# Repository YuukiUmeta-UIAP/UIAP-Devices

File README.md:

# Album of UIAP Devices

You can find everthing about UIAP Devices

- Source
- Library
- [Application](app)

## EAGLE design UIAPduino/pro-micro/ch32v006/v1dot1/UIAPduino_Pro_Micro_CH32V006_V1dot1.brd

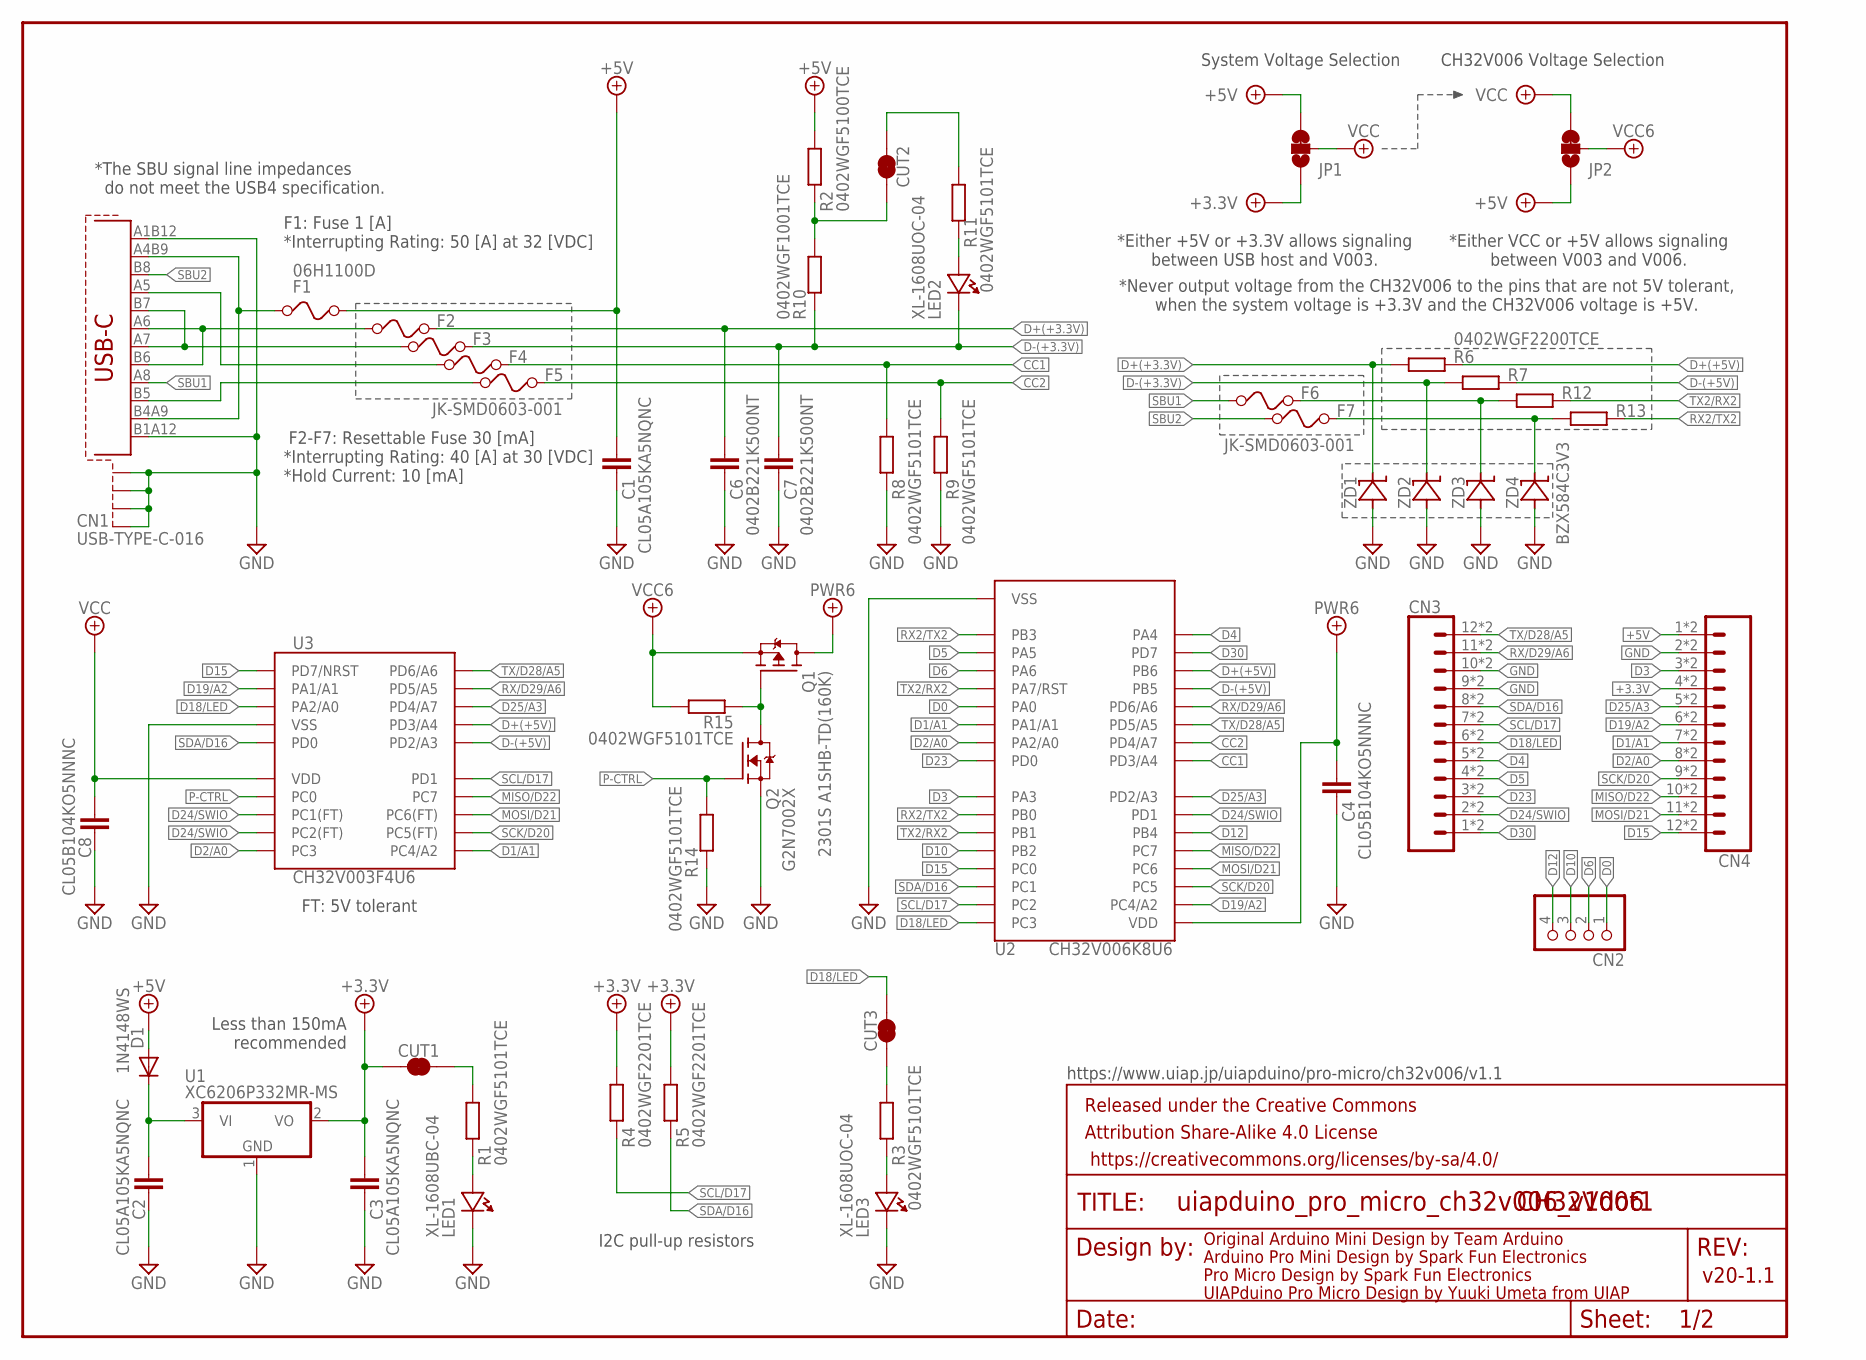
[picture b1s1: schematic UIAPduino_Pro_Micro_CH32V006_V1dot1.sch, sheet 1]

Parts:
C1, C2, C3: CL05A105KA5NQNC; 1005
C4, C8: CL05B104KO5NNNC; 1005
C6, C7: 0402B221K500NT; 1005
CN1: USB-TYPE-C-016
CN2: PH-2X2; 2X02
CN3, CN4: CONN_12CASTLE_0.9MM; 1X12_CASTELLATED_0.9MM
CUT1, CUT2, CUT3: SMT-JP-2-NC; SMT-JUMPER_2_NC_SILK_ROUND
D1: 1N4148WS; SOD-523
F1: 06H1100D; 1608
F2, F3, F4, F5, F6, F7: JK-SMD0603-001; 1608; JLCPCB-PART-# C2687114
FRAME1: FRAME-LETTER; CREATIVE_COMMONS
JP1, JP2: SMT-JP-3-NO-NC; SMT-JUMPER_3_1-NC_TRACE_SILK
LED1: XL-1608UBC-04; 1608-LED
LED2, LED3: XL-1608UOC-04; 1608-LED
Q1: 2301S A1SHB-TD(160K); SOT-23F_TOS-L
Q2: G2N7002X; SOT-523
R1, R3, R8, R9, R11, R14, R15: 0402WGF5101TCE; 1005
R2: 0402WGF5100TCE; 1005
R4, R5: 0402WGF2201TCE; 1005
R6, R7, R12, R13: 0402WGF2200TCE; 1005
R10: 0402WGF1001TCE; 1005
U1: XC6206P332MR-MS; SOT-23F_TOS-L
U2: CH32V006K8U6; QFN32-400X400X100
U3: CH32V003F4U6; QFN20-300X300X100-L
ZD1, ZD2, ZD3, ZD4: BZX584C3V3; SOD-523

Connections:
+3.3V: C3.1, CN4.4, CN4.4B (4), CUT1.2, JP1.1, R4.2, R5.2, U1.2 (VO)
+5V: C1.1, CN4.1, CN4.1B (1), D1.2 (A), F1.2, JP1.3, JP2.1, R2.2
CC1: F4.2, R8.2, U2.25 (PD3/A4)
CC2: F5.2, R9.2, U2.26 (PD4/A7)
CUT1: CUT1.1, R1.2
D0: CN2.1, U2.5 (PA0)
D1: C2.1, D1.1 (C), U1.3 (VI)
D1/A1: CN4.7, CN4.7B (7), U2.6 (PA1/A1), U3.11 (PC4/A2)
D2/A0: CN4.8, CN4.8B (8), U2.7 (PA2/A0), U3.10 (PC3)
D3: CN4.3, CN4.3B (3), U2.9 (PA3)
D4: CN3.5, CN3.5B (5), U2.32 (PA4)
D5: CN3.4, CN3.4B (4), U2.2 (PA5)
D6: CN2.2, U2.3 (PA6)
D10: CN2.3, U2.12 (PB2)
D12: CN2.4, U2.22 (PB4)
D15: CN4.12, CN4.12B (12), U2.13 (PC0), U3.1 (PD7/NRST)
D18/LED: CN3.6, CN3.6B (6), CUT3.1, U2.16 (PC3), U3.3 (PA2/A0)
D19/A2: CN4.6, CN4.6B (6), U2.18 (PC4/A2), U3.2 (PA1/A1)
D23: CN3.3, CN3.3B (3), U2.8 (PD0)
D24/SWIO: CN3.2, CN3.2B (2), U2.23 (PD1), U3.8 (PC1(FT)), U3.9 (PC2(FT))
D25/A3: CN4.5, CN4.5B (5), U2.24 (PD2/A3), U3.18 (PD4/A7)
D30: CN3.1, CN3.1B (1), U2.31 (PD7)
D+(+3.3V): C6.1, F2.2, R6.1, ZD1.1 (C)
D+(+5V): R6.2, U2.30 (PB6), U3.17 (PD3/A4)
D-(+3.3V): C7.1, F3.2, LED2.2 (C), R7.1, R10.1, ZD2.1 (C)
D-(+5V): R7.2, U2.29 (PB5), U3.16 (PD2/A3)
F1: CN1.A4B9 (VBUS), CN1.B4A9 (VBUS), F1.1
GND: C1.2, C2.2, C3.2, C4.2, C6.2, C7.2, C8.2, CN1.A1B12 (GND), CN1.B1A12 (GND), CN1.S1, CN1.S1B (S1), CN1.S2, CN1.S2B (S2), CN1.S3, CN1.S3B (S3), CN1.S4, CN1.S4B (S4), CN3.9, CN3.9B (9), CN3.10, CN3.10B (10), CN4.2, CN4.2B (2), LED1.2 (C), LED3.2 (C), Q2.2 (S), R8.1, R9.1, R14.1, U1.1 (GND), U2.0 (VSS), U2.P-VIA$1 (VSS), U2.P-VIA$5 (VSS), U2.P-VIA$6 (VSS), U2.P-VIA$8 (VSS), U2.P-VIA$9 (VSS), U3.4 (VSS), U3.21 (VSS), U3.P-VIA$1 (VSS), ZD1.2 (A), ZD2.2 (A), ZD3.2 (A), ZD4.2 (A)
MISO/D22: CN4.10, CN4.10B (10), U2.21 (PC7), U3.14 (PC7)
MOSI/D21: CN4.11, CN4.11B (11), U2.20 (PC6), U3.13 (PC6(FT))
unnamed: CN1.A6 (DP1), CN1.B6 (DP2), F2.1
unnamed: CUT2.2, R2.1, R10.2
unnamed: Q1.1 (G), Q2.3 (D), R15.1
unnamed: CN1.A7 (DN1), CN1.B7 (DN2), F3.1
unnamed: CN1.A5 (CC1), F4.1
unnamed: F6.2, R12.1, ZD3.1 (C)
unnamed: LED3.1 (A), R3.1
unnamed: CN1.B5 (CC2), F5.1
unnamed: LED2.1 (A), R11.1
unnamed: CUT3.2, R3.2
unnamed: CUT2.1, R11.2
unnamed: F7.2, R13.1, ZD4.1 (C)
unnamed: LED1.1 (A), R1.1
P-CTRL: Q2.1 (G), R14.2, U3.7 (PC0)
PWR6: C4.1, Q1.3 (D), U2.17 (VDD)
RX2/TX2: R13.2, U2.1 (PB3), U2.10 (PB0)
RX/D29/A6: CN3.11, CN3.11B (11), U2.28 (PD6/A6), U3.19 (PD5/A5)
SBU1: CN1.A8 (SBU1), F6.1
SBU2: CN1.B8 (SBU2), F7.1
SCK/D20: CN4.9, CN4.9B (9), U2.19 (PC5), U3.12 (PC5(FT))
SCL/D17: CN3.7, CN3.7B (7), R4.1, U2.15 (PC2), U3.15 (PD1)
SDA/D16: CN3.8, CN3.8B (8), R5.1, U2.14 (PC1), U3.5 (PD0)
TX2/RX2: R12.2, U2.4 (PA7/RST), U2.11 (PB1)
TX/D28/A5: CN3.12, CN3.12B (12), U2.27 (PD5/A5), U3.20 (PD6/A6)
VCC: C8.1, JP1.2, JP2.3, U3.6 (VDD)
VCC6: JP2.2, Q1.2 (S), R15.2

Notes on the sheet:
Original Arduino Mini Design by Team Arduino
Arduino Pro Mini Design by Spark Fun Electronics
Less than 150mA recommended
Pro Micro Design by Spark Fun Electronics
CH32V006 Voltage Selection
v20-1.1
F2-F7: Resettable Fuse 30 [mA] *Interrupting Rating: 40 [A] at 30 [VDC] *Hold Current: 10 [mA]
I2C pull-up resistors
UIAPduino Pro Micro Design by Yuuki Umeta from UIAP
https://www.uiap.jp/uiapduino/pro-micro/ch32v006/v1.1
F1: Fuse 1 [A] *Interrupting Rating: 50 [A] at 32 [VDC]
*Either +5V or +3.3V allows signaling between USB host and V003.
CH32V006
System Voltage Selection
*Either VCC or +5V allows signaling between V003 and V006.
FT: 5V tolerant
*Never output voltage from the CH32V006 to the pins that are not 5V tolerant, when the system voltage is +3.3V and the CH32V006 voltage is +5V.
*The SBU signal line impedances do not meet the USB4 specification.

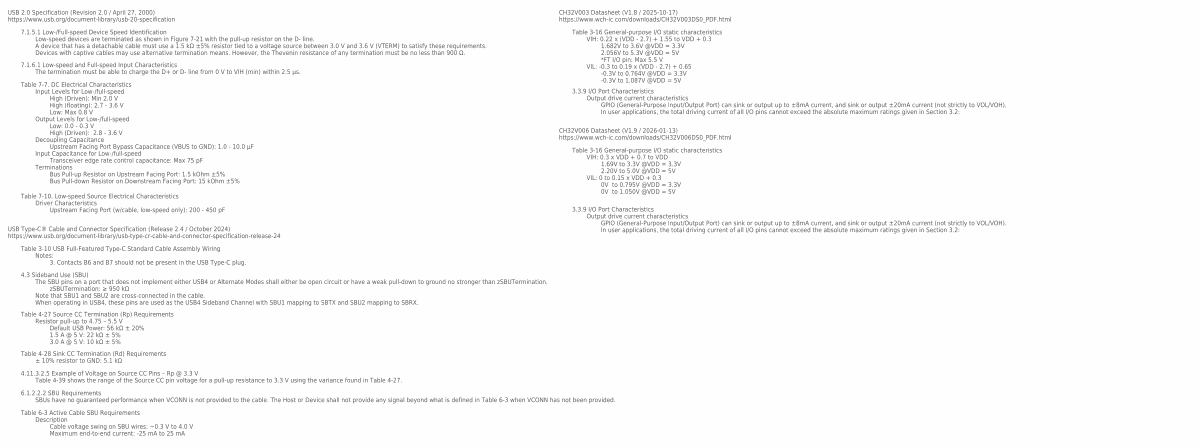
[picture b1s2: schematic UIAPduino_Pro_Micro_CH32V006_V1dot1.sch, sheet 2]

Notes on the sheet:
Table 7-10. Low-speed Source Electrical Characteristics Driver Characteristics Upstream Facing Port (w/cable, low-speed only): 200 - 450 pF
Table 7-7. DC Electrical Characteristics Input Levels for Low-/full-speed High (Driven): Min 2.0 V High (floating): 2.7 - 3.6 V Low: Max 0.8 V Output Levels for Low-/full-speed Low: 0.0 - 0.3 V High (Driven): 2.8 - 3.6 V Decoupling Capacitance Upstream Facing Port Bypass Capacitance (VBUS to GND): 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
7.1.6.1 Low-speed and Full-speed Input Characteristics The termination must be able to charge the D+ or D- line from 0 V to VIH (min) within 2.5 µs.
7.1.5.1 Low-/Full-speed Device Speed Identification Low-speed devices are terminated as shown in Figure 7-21 with the pull-up resistor on the D- line. A device that has a detachable cable must use a 1.5 kΩ ±5% resistor tied to a voltage source between 3.0 V and 3.6 V (VTERM) to satisfy these requir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
Table 4-28 Sink CC Termination (Rd) Requirements ± 10% resistor to GND: 5.1 kΩ
Table 4-27 Source CC Termination (Rp) Requirements Resistor pull-up to 4.75 – 5.5 V Default USB Power: 56 kΩ ± 20% 1.5 A @ 5 V: 22 kΩ ± 5% 3.0 A @ 5 V: 10 kΩ ± 5%
USB Type-C® Cable and Connector Specification (Release 2.4 / October 2024) https://www.usb.org/document-library/usb-type-cr-cable-and-connector-specification-release-24
USB 2.0 Specification (Revision 2.0 / April 27, 2000) https://www.usb.org/document-library/usb-20-specification
4.11.3.2.5 Example of Voltage on Source CC Pins – Rp @ 3.3 V Table 4-39 shows the range of the Source CC pin voltage for a pull-up resistance to 3.3 V using the variance found in Table 4-27.
CH32V006 Datasheet (V1.9 / 2026-01-13) https://www.wch-ic.com/downloads/CH32V006DS0_PDF.html
Table 3-16 General-purpose I/O static characteristics VIH: 0.3 x VDD + 0.7 to VDD 1.69V to 3.3V @VDD = 3.3V 2.20V to 5.0V @VDD = 5V VIL: 0 to 0.15 x VDD + 0.3 0V to 0.795V @VDD = 3.3V 0V to 1.050V @VDD = 5V
Table 3-10 USB Full-Featured Type-C Standard Cable Assembly Wiring Notes: 3. Contacts B6 and B7 should not be present in the USB Type-C plug.
4.3 Sideband Use (SBU) The SBU pins on a port that does not implement either USB4 or Alternate Modes shall either be open circuit or have a weak pull-down to ground no stronger than zSBUTermination. zSBUTermination: ≥ 950 kΩ Note that SBU1 and SBU2 are cross-connected in the cable. When operating i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
3.3.9 I/O Port Characteristics Output drive current characteristics GPIO (General-Purpose Input/Output Port) can sink or output up to ±8mA current, and sink or output ±20mA current (not strictly to VOL/VOH). In user applications, the total driving current of all I/O pins cannot exceed the absolute 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
6.1.2.2.2 SBU Requirements SBUs have no guaranteed performance when VCONN is not provided to the cable. The Host or Device shall not provide any signal beyond what is defined in Table 6-3 when VCONN has not been provided.
Table 6-3 Active Cable SBU Requirements Description Cable voltage swing on SBU wires: −0.3 V to 4.0 V Maximum end-to-end current: -25 mA to 25 mA
CH32V003 Datasheet (V1.8 / 2025-10-17) https://www.wch-ic.com/downloads/CH32V003DS0_PDF.html
Table 3-16 General-purpose I/O static characteristics VIH: 0.22 x (VDD - 2.7) + 1.55 to VDD + 0.3 1.682V to 3.6V @VDD = 3.3V 2.056V to 5.3V @VDD = 5V *FT I/O pin: Max 5.5 V VIL: -0.3 to 0.19 x (VDD - 2.7) + 0.65 -0.3V to 0.764V @VDD = 3.3V -0.3V to 1.087V @VDD = 5V

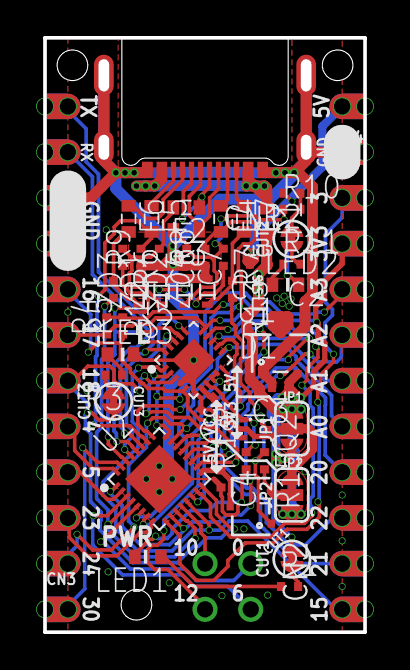
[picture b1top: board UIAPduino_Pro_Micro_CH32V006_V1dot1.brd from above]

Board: 2 copper layers, 17.8 x 33.0 mm, 52 parts (0 on the bottom side), 56 nets.

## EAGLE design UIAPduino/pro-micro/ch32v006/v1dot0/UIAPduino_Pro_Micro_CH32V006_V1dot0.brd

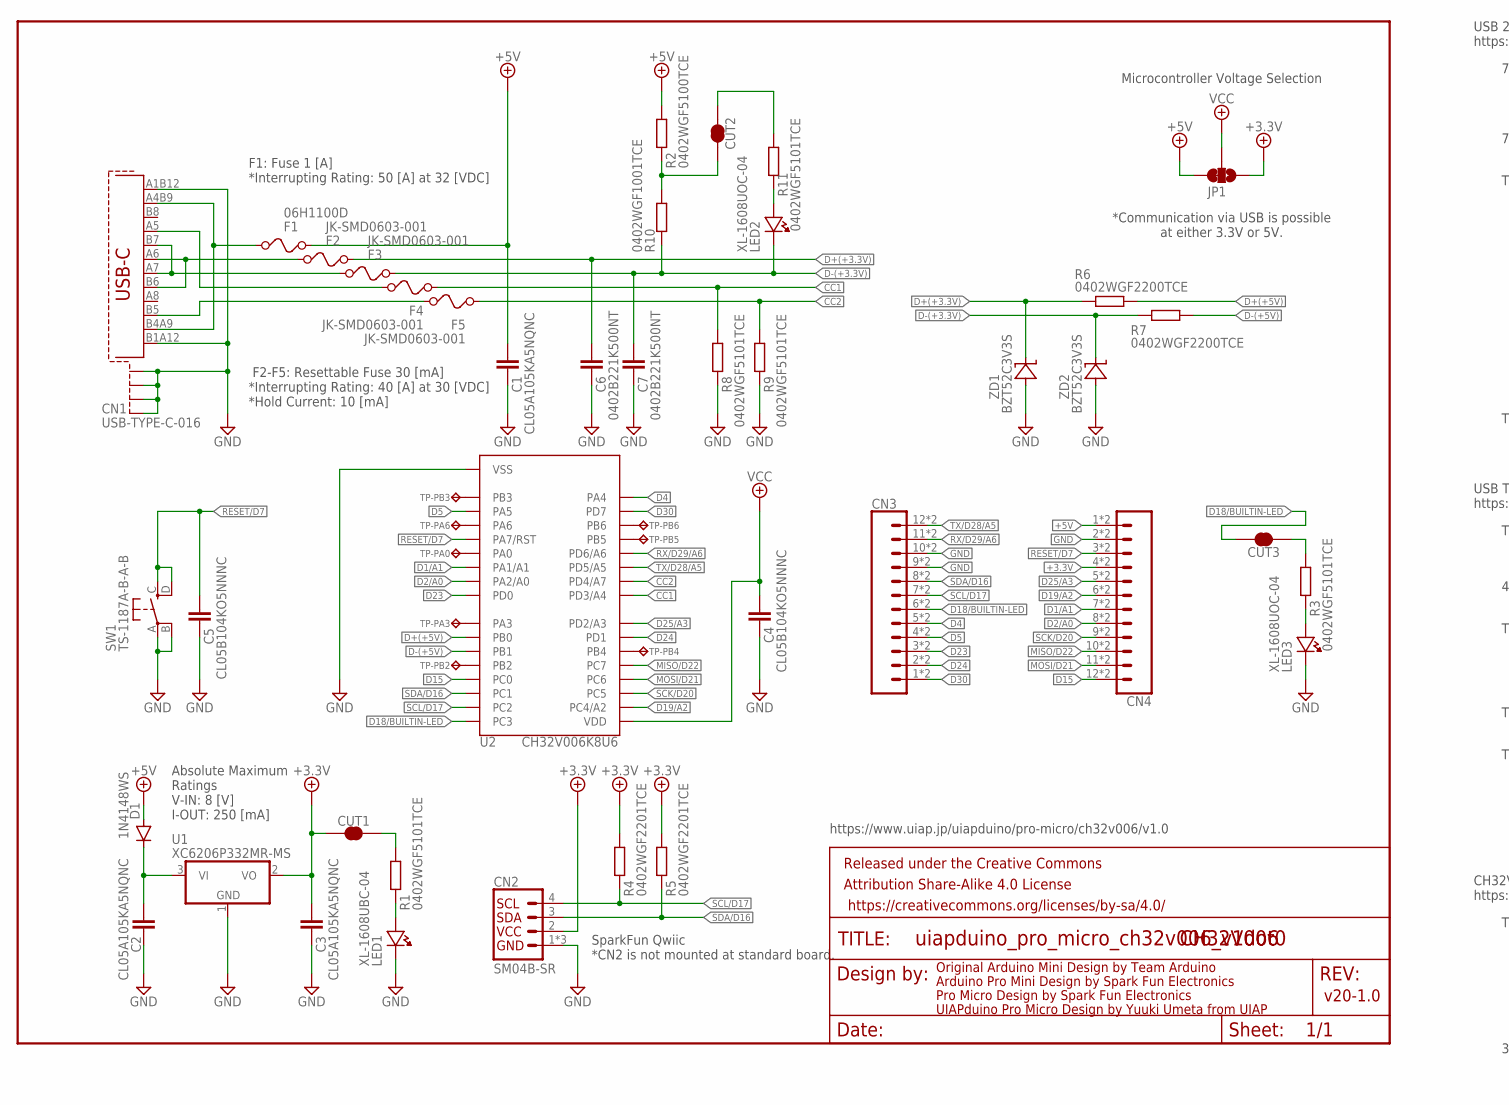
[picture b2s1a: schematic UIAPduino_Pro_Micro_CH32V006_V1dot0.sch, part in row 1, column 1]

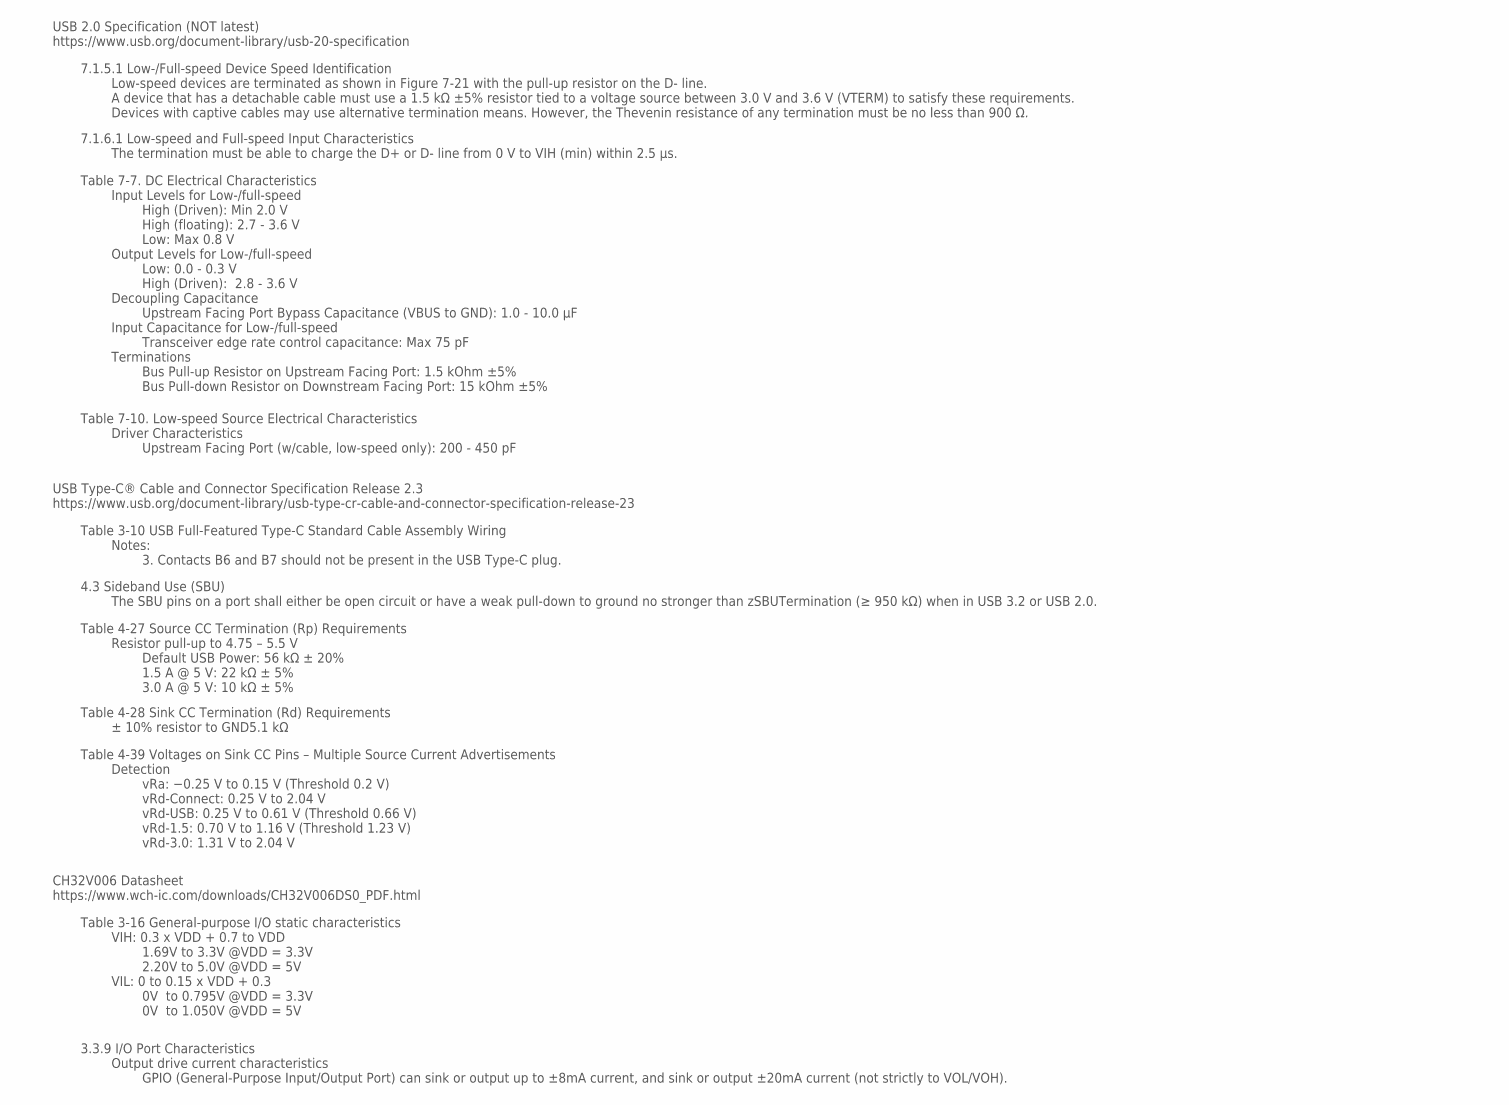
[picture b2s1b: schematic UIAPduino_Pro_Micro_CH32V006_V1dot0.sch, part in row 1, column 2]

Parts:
C1, C2, C3: CL05A105KA5NQNC; 1005
C4, C5: CL05B104KO5NNNC; 1005
C6, C7: 0402B221K500NT; 1005
CN1: USB-TYPE-C-016
CN2: SM04B-SR; JST04_1MM_RA
CN3, CN4: CONN_12CASTLE_0.9MM; 1X12_CASTELLATED_0.9MM
CUT1, CUT2, CUT3: SMT-JP-2-NC; SMT-JUMPER_2_NC_SILK_ROUND
D1: 1N4148WS; SOD323-R; JLCPCB-PART-# C2128
F1: 06H1100D; 1608
F2, F3, F4, F5: JK-SMD0603-001; 1608
FRAME1: FRAME-LETTER; CREATIVE_COMMONS
JP1: SMT-JP-3-NO-NC; SMT-JUMPER_3_1-NC_TRACE_SILK
LED1: XL-1608UBC-04; 1608-LED
LED2, LED3: XL-1608UOC-04; 1608-LED
R1, R3, R8, R9, R11: 0402WGF5101TCE; 1005
R2: 0402WGF5100TCE; 1005
R4, R5: 0402WGF2201TCE; 1005
R6, R7: 0402WGF2200TCE; 1005
R10: 0402WGF1001TCE; 1005
SW1: TS-1187A-B-A-B
TP-PA0, TP-PA3, TP-PA6: TPTP06R; TP06R
TP-PB2, TP-PB3, TP-PB4, TP-PB5, TP-PB6: TPTP06R; TP06R
U1: XC6206P332MR-MS; SOT-23F_TOS
U2: CH32V006K8U6; QFN40P400X400X100-33T270
ZD1, ZD2: BZT52C3V3S; SOD323-R

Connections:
+3.3V: C3.1, CN2.2, CN4.4, CN4.4B (4), CUT1.2, JP1.1, R4.2, R5.2, U1.2 (VO)
+5V: C1.1, CN4.1, CN4.1B (1), D1.A, F1.2, JP1.3, R2.2
CC1: F4.2, R8.2, U2.25 (PD3/A4)
CC2: F5.2, R9.2, U2.26 (PD4/A7)
D1/A1: CN4.7, CN4.7B (7), U2.6 (PA1/A1)
D2/A0: CN4.8, CN4.8B (8), U2.7 (PA2/A0)
D4: CN3.5, CN3.5B (5), U2.32 (PA4)
D5: CN3.4, CN3.4B (4), U2.2 (PA5)
D15: CN4.12, CN4.12B (12), U2.13 (PC0)
D18/BUILTIN-LED: CN3.6, CN3.6B (6), CUT3.1, U2.16 (PC3)
D19/A2: CN4.6, CN4.6B (6), U2.18 (PC4/A2)
D23: CN3.3, CN3.3B (3), U2.8 (PD0)
D24: CN3.2, CN3.2B (2), U2.23 (PD1)
D25/A3: CN4.5, CN4.5B (5), U2.24 (PD2/A3)
D30: CN3.1, CN3.1B (1), U2.31 (PD7)
D+(+3.3V): C6.1, F2.2, R6.1, ZD1.C
D+(+5V): R6.2, U2.10 (PB0)
D-(+3.3V): C7.1, F3.2, LED2.2 (C), R7.1, R10.1, ZD2.C
D-(+5V): R7.2, U2.11 (PB1)
F1: CN1.A4B9 (VBUS), CN1.B4A9 (VBUS), F1.1
GND: C1.2, C2.2, C3.2, C4.2, C5.2, C6.2, C7.2, CN1.A1B12 (GND), CN1.B1A12 (GND), CN1.S1, CN1.S1B (S1), CN1.S2, CN1.S2B (S2), CN1.S3, CN1.S3B (S3), CN1.S4, CN1.S4B (S4), CN2.1, CN2.NC1 (1), CN2.NC2 (1), CN3.9, CN3.9B (9), CN3.10, CN3.10B (10), CN4.2, CN4.2B (2), LED1.2 (C), LED3.2 (C), R8.1, R9.1, SW1.A, SW1.B (P1), U1.1 (GND), U2.0 (VSS), U2.P-VIA$1 (VSS), U2.P-VIA$2 (VSS), U2.P-VIA$3 (VSS), U2.P-VIA$4 (VSS), U2.P-VIA$5 (VSS), U2.P-VIA$6 (VSS), U2.P-VIA$7 (VSS), U2.P-VIA$8 (VSS), U2.P-VIA$9 (VSS), ZD1.A, ZD2.A
MISO/D22: CN4.10, CN4.10B (10), U2.21 (PC7)
MOSI/D21: CN4.11, CN4.11B (11), U2.20 (PC6)
unnamed: CN1.A6 (DP1), CN1.B6 (DP2), F2.1
unnamed: CUT2.2, R2.1, R10.2
unnamed: C2.1, D1.C, U1.3 (VI)
unnamed: CN1.A7 (DN1), CN1.B7 (DN2), F3.1
unnamed: CN1.A5 (CC1), F4.1
unnamed: CUT1.1, R1.2
unnamed: LED3.1 (A), R3.1
unnamed: CN1.B5 (CC2), F5.1
unnamed: LED2.1 (A), R11.1
unnamed: CUT3.2, R3.2
unnamed: CUT2.1, R11.2
unnamed: TP-PB3.TP, U2.1 (PB3)
unnamed: TP-PA6.TP, U2.3 (PA6)
unnamed: TP-PA0.TP, U2.5 (PA0)
unnamed: TP-PA3.TP, U2.9 (PA3)
unnamed: TP-PB2.TP, U2.12 (PB2)
unnamed: TP-PB4.TP, U2.22 (PB4)
unnamed: TP-PB5.TP, U2.29 (PB5)
unnamed: TP-PB6.TP, U2.30 (PB6)
unnamed: LED1.1 (A), R1.1
RESET/D7: C5.1, CN4.3, CN4.3B (3), SW1.C (S), SW1.D (S1), U2.4 (PA7/RST)
RX/D29/A6: CN3.11, CN3.11B (11), U2.28 (PD6/A6)
SCK/D20: CN4.9, CN4.9B (9), U2.19 (PC5)
SCL/D17: CN2.4, CN3.7, CN3.7B (7), R4.1, U2.15 (PC2)
SDA/D16: CN2.3, CN3.8, CN3.8B (8), R5.1, U2.14 (PC1)
TX/D28/A5: CN3.12, CN3.12B (12), U2.27 (PD5/A5)
VCC: C4.1, JP1.2, U2.17 (VDD)

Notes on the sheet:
Original Arduino Mini Design by Team Arduino
Arduino Pro Mini Design by Spark Fun Electronics
Absolute Maximum Ratings V-IN: 8 [V] I-OUT: 250 [mA]
Pro Micro Design by Spark Fun Electronics
Microcontroller Voltage Selection
v20-1.0
F2-F5: Resettable Fuse 30 [mA] *Interrupting Rating: 40 [A] at 30 [VDC] *Hold Current: 10 [mA]
Table 7-10. Low-speed Source Electrical Characteristics Driver Characteristics Upstream Facing Port (w/cable, low-speed only): 200 - 450 pF
Table 7-7. DC Electrical Characteristics Input Levels for Low-/full-speed High (Driven): Min 2.0 V High (floating): 2.7 - 3.6 V Low: Max 0.8 V Output Levels for Low-/full-speed Low: 0.0 - 0.3 V High (Driven): 2.8 - 3.6 V Decoupling Capacitance Upstream Facing Port Bypass Capacitance (VBUS to GND): 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
7.1.6.1 Low-speed and Full-speed Input Characteristics The termination must be able to charge the D+ or D- line from 0 V to VIH (min) within 2.5 µs.
7.1.5.1 Low-/Full-speed Device Speed Identification Low-speed devices are terminated as shown in Figure 7-21 with the pull-up resistor on the D- line. A device that has a detachable cable must use a 1.5 kΩ ±5% resistor tied to a voltage source between 3.0 V and 3.6 V (VTERM) to satisfy these requir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
Table 4-28 Sink CC Termination (Rd) Requirements ± 10% resistor to GND5.1 kΩ
Table 4-27 Source CC Termination (Rp) Requirements Resistor pull-up to 4.75 – 5.5 V Default USB Power: 56 kΩ ± 20% 1.5 A @ 5 V: 22 kΩ ± 5% 3.0 A @ 5 V: 10 kΩ ± 5%
USB Type-C® Cable and Connector Specification Release 2.3 https://www.usb.org/document-library/usb-type-cr-cable-and-connector-specification-release-23
USB 2.0 Specification (NOT latest) https://www.usb.org/document-library/usb-20-specification
Table 4-39 Voltages on Sink CC Pins – Multiple Source Current Advertisements Detection vRa: −0.25 V to 0.15 V (Threshold 0.2 V) vRd-Connect: 0.25 V to 2.04 V vRd-USB: 0.25 V to 0.61 V (Threshold 0.66 V) vRd-1.5: 0.70 V to 1.16 V (Threshold 1.23 V) vRd-3.0: 1.31 V to 2.04 V
CH32V006 Datasheet https://www.wch-ic.com/downloads/CH32V006DS0_PDF.html
Table 3-16 General-purpose I/O static characteristics VIH: 0.3 x VDD + 0.7 to VDD 1.69V to 3.3V @VDD = 3.3V 2.20V to 5.0V @VDD = 5V VIL: 0 to 0.15 x VDD + 0.3 0V to 0.795V @VDD = 3.3V 0V to 1.050V @VDD = 5V
SparkFun Qwiic *CN2 is not mounted at standard board.
Table 3-10 USB Full-Featured Type-C Standard Cable Assembly Wiring Notes: 3. Contacts B6 and B7 should not be present in the USB Type-C plug.
4.3 Sideband Use (SBU) The SBU pins on a port shall either be open circuit or have a weak pull-down to ground no stronger than zSBUTermination (≥ 950 kΩ) when in USB 3.2 or USB 2.0.
UIAPduino Pro Micro Design by Yuuki Umeta from UIAP
https://www.uiap.jp/uiapduino/pro-micro/ch32v006/v1.0
F1: Fuse 1 [A] *Interrupting Rating: 50 [A] at 32 [VDC]
*Communication via USB is possible at either 3.3V or 5V.
3.3.9 I/O Port Characteristics Output drive current characteristics GPIO (General-Purpose Input/Output Port) can sink or output up to ±8mA current, and sink or output ±20mA current (not strictly to VOL/VOH).
CH32V006

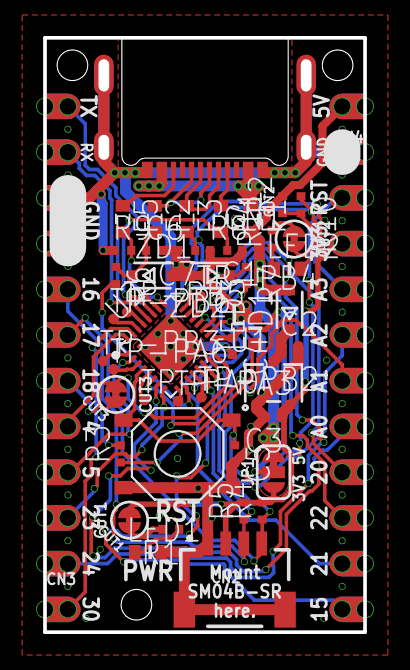
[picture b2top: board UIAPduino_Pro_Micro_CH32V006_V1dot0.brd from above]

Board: 2 copper layers, 17.8 x 33.0 mm, 49 parts (0 on the bottom side), 50 nets.

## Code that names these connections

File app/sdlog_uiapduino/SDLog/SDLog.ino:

/**
 * SDLog.ino — UART serial data logger for UIAPduino
 *
 * SPDX-License-Identifier: MIT
 * Copyright (c) 2026 tarosay
 *
 * Overview:
 *   Receives data on UART RX and writes it to a microSD card.
 *   A new log file is created on every power cycle.
 *
 * Log files:
 *   Files are created in order: LOG00001.TXT, LOG00002.TXT, ...
 *   Synced data is retained after power-off.
 *
 * Baud rate (CONFIG.TXT):
 *   Place CONFIG.TXT on the SD card to set the baud rate.
 *   Format: 9600,26,3,0  (only the first value is used)
 *   If the file does not exist, 9600 bps is used and CONFIG.TXT is
 *   created automatically. Baud rates of 300 bps or higher can be specified.
 *
 * LED behavior:
 *   Fast blink  — error (SD init failed, cannot create log file, etc.)
 *   Blink       — writing data to SD
 *   Steady      — waiting for data
 *
 * Board and IDE settings:
 *   Board Manager URL:
 *     https://github.com/tarosay/board_manager_files/raw/main/package_uiap_hid_index.json
 *   Board : Tools > Board > UIAP_HID > HID ProMicro CH32V003
 *   USB   : Tools > USB > No USB (SD log / UART only)
 *   FQBN  : UIAP_HID:ch32v:CH32V003:usb=nousb,opt=oslto
 *
 * Wiring — UIAPduino to microSD card adapter:
 *
 *   UIAPduino        SD card adapter
 *   ─────────────────────────────────
 *   A2  (PC4, pin 6)  →  CS   (DAT3)
 *   8   (PC6)         →  MOSI (CMD / DI)
 *   7   (PC5)         →  SCK  (CLK)
 *   9   (PC7)         →  MISO (DAT0 / DO)
 *   3V3               →  VDD
 *   GND               →  VSS
 *
 * UART (data input):
 *   RX  PD6  — connect to TX of the device to be logged
 *   TX  PD5  — not used for logging (available for debug output)
 */

#include <Arduino.h>
#include <SDmin.h>
#include "UIAPSerial.h"

#define LED_BUILTIN 2
static const uint8_t  PIN_SS   = 6;   // CS = A2 = PC4
static const uint8_t  BUF_SIZE = 64;
static const uint32_t IDLE_MS  = 200;   // flush after this many ms of inactivity

static uint8_t  rxBuf[BUF_SIZE];
static uint8_t  rxLen      = 0;
static uint32_t lastRxTime = 0;
static char     logFilename[13];   // "LOG00001.TXT\0"

// ── Read baud rate from CONFIG.TXT (create with default if missing) ───────────
static const char CONFIG_DEFAULT[] = "9600,26,3,0\r\n";

static uint32_t load_config(void) {
  // File not found → create with default value and return 9600
  if (!sm_open_r("CONFIG.TXT")) {
    if (sm_open_w("CONFIG.TXT")) {
      sm_write((const uint8_t*)CONFIG_DEFAULT, sizeof(CONFIG_DEFAULT) - 1);
      sm_close_w();
    }
    return 9600UL;
  }

  // File found → read the first field (baud rate)
  char buf[8];
  uint8_t n = 0;
  uint8_t b;
  while (n < (uint8_t)(sizeof(buf) - 1)) {
    if (sm_read(&b, 1) != 1) break;
    if ((char)b == ',' || (char)b == '\r' || (char)b == '\n') break;
    buf[n++] = (char)b;
  }
  sm_close_r();
  buf[n] = '\0';

  uint32_t baud = 0;
  for (uint8_t i = 0; i < n; i++) {
    if (buf[i] >= '0' && buf[i] <= '9')
      baud = baud * 10 + (uint32_t)(buf[i] - '0');
  }
  return (baud >= 300UL) ? baud : 9600UL;
}

// ── Utilities ─────────────────────────────────────────────────────────────────
static void error_blink(void) {
  while (1) {
    digitalWrite(LED_BUILTIN, HIGH); delay(200);
    digitalWrite(LED_BUILTIN, LOW);  delay(200);
  }
}

static void make_logname(char *buf, uint16_t n) {
  buf[0]='L'; buf[1]='O'; buf[2]='G';
  buf[3] = '0' + (n / 10000) % 10;
  buf[4] = '0' + (n /  1000) % 10;
  buf[5] = '0' + (n /   100) % 10;
  buf[6] = '0' + (n /    10) % 10;
  buf[7] = '0' + (n        ) % 10;
  buf[8]='.'; buf[9]='T'; buf[10]='X'; buf[11]='T'; buf[12]='\0';
}

// ── Setup ─────────────────────────────────────────────────────────────────────
void setup() {
  pinMode(LED_BUILTIN, OUTPUT);
  digitalWrite(LED_BUILTIN, LOW);

  if (!sm_init(PIN_SS)) error_blink();
  if (!sm_mount())      error_blink();

  uint32_t baud = load_config();

  // Find the first unused filename and open it for writing (stays open until power-off)
  // uart.begin() is called AFTER the file is open so no SPI operation occurs during
  // UART reception.
  bool found = false;
  for (uint16_t i = 1; i <= 65534u; i++) {
    make_logname(logFilename, i);
    if (!sm_open_r(logFilename)) {
      found = sm_open_w(logFilename);
      break;
    }
    sm_close_r();
  }
  if (!found) error_blink();

  uart.begin(baud);
}

// ── Loop: UART → SD ───────────────────────────────────────────────────────────
//
// Design note — open once in setup(), sync at each burst end:
//   The file is opened by sm_open_w() in setup() before uart.begin().
//   No SPI operation ever occurs while UART reception is active.
//
//   sm_sync_w() is called after each burst (IDLE_MS of inactivity) or when
//   rxBuf is full. It flushes the partial sector and updates the directory
//   size in ~4 ms regardless of file length (no FAT chain walk).
//
//   On power cut, at most BUF_SIZE (64) bytes currently in rxBuf may be lost.
//   All data already passed to sm_sync_w() is committed to the SD card.
//
void loop() {
  static uint8_t ledSt = 0;
  bool got = false;

  while (uart.available()) {
    if (rxLen < BUF_SIZE) {
      rxBuf[rxLen++] = uart.read();
      got = true;
    } else {
      break;
    }
  }

  if (got) lastRxTime = millis();

  // Buffer full → write only (UART may still be active; sm_sync_w must not run here)
  if (rxLen >= BUF_SIZE) {
    sm_write(rxBuf, rxLen); rxLen = 0;
    ledSt ^= 1; digitalWrite(LED_BUILTIN, ledSt);
    return;
  }

  // Idle for IDLE_MS → write buffered data and sync
  if (rxLen > 0 && (uint32_t)(millis() - lastRxTime) >= IDLE_MS) {
    sm_write(rxBuf, rxLen); rxLen = 0;
    sm_sync_w();   // ~4 ms: flush sector + update dir size
    ledSt ^= 1; digitalWrite(LED_BUILTIN, ledSt);
  }
}

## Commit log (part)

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2024-09-15 Made repository to store with license files.
2024-09-15 Create LICENSE.txt
    Added license file.
2025-06-17 Moved directory to reflect repository name change
2025-06-17 Added user library: - .lbr is for EAGLE or Autodesk Fusion - .LB3 is for BSch3V
2025-06-19 Added KiCad library: - Symbol (.kicad_sym) - Footprint (.pretty)
2025-09-15 Add Fritzing library
2025-09-30 Add application directory
2025-09-30 Change message about the right
2025-09-30 Change tiny
2025-09-30 Add template
2025-09-30 Move dummy files from template folder to app folder
2025-09-30 Revert the location of the dummy file back because symbolic links are not good for some environment
2025-09-30 Add commands of the way to add own app to this repository
2025-09-30 Fix cd command
2025-09-30 Add English
2025-09-30 Fixed language separation
2025-09-30 Fix anchor text
2025-09-30 Add split-keyboard app
2025-09-30 Add reproducible app link
2025-09-30 Fix text and layout on split-keyboard README.md
2025-09-30 Fix tiny thing
2025-09-30 Add example on How to Add section
2025-09-30 Fix typo
2025-09-30 Add memo to split-keyboard README.md
2025-10-01 Change from only source code to post with source code about simple spectrum analyzer and Morse code decoder
2025-10-02 Add details that are the programs and a way to build it
2025-10-08 Change details in the split-keyboard README.md
2025-10-15 Add Breakout to reproducible app README.md
2025-10-21 Add "ADCTOUCH + USB-MIDI example for UIAPDuino" to Just Links on app/README.md
2025-11-04 Add a report using OLED SSD1306 to Just Links on app/README.md
2025-11-04 Add "UIAPduino Pro Micro Sample Programs" to Just Links on app/README.md
2025-11-19 Add "UIAPduino Pro Micro CH32V006" version 1.0
2026-02-19 Add GitHub link for UIAPduino breakout board
2026-02-19 Add new link to UIAPduino video review
2026-02-20 Add "UIAPduino Pro Micro CH32V006" version 1.1
2026-02-24 Add some links on app/README.md
2026-03-04 Add Clone and Manufacture on app
2026-03-04 Add new link to demo written in Rust
2026-03-09 uiap-hal-templateのリンクを追加
2026-03-16 Fix a link URL on app/README.md
2026-04-12 Add 'Videos' section to README.md
    Added a new section for videos with automatically generated tags.

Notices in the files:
parts and their libraries:
SparkFun-Aesthetics: Licensing: CC v3.0 Share-Alike You are welcome to use this library for commercial purposes.
SparkFun-Aesthetics: Released under the Creative Commons Attribution Share-Alike 4.0 License
SparkFun-Aesthetics: https://creativecommons.org/licenses/by-sa/4.0
